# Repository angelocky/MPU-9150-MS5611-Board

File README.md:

MPU-9150-MS5611-Board
=====================
For the MPU-9150 and MS5611 Breakout Board. 

Arduino Library for the MPU-9150: [https://github.com/sparkfun/MPU-9150_Breakout/tree/master/firmware](https://github.com/sparkfun/MPU-9150_Breakout/tree/master/firmware)

Arduino Library for the MS5611 from Varesano.net: [http://www.varesano.net/files/FreeIMU-20121122_1126.zip](http://www.varesano.net/files/FreeIMU-20121122_1126.zip)

"MPU_9150_5611_example.ino" is an example sketch, to show functionality of the board. Individual example sketches can be found in their respective libraries.

Credit is due to the respective creators of the code.

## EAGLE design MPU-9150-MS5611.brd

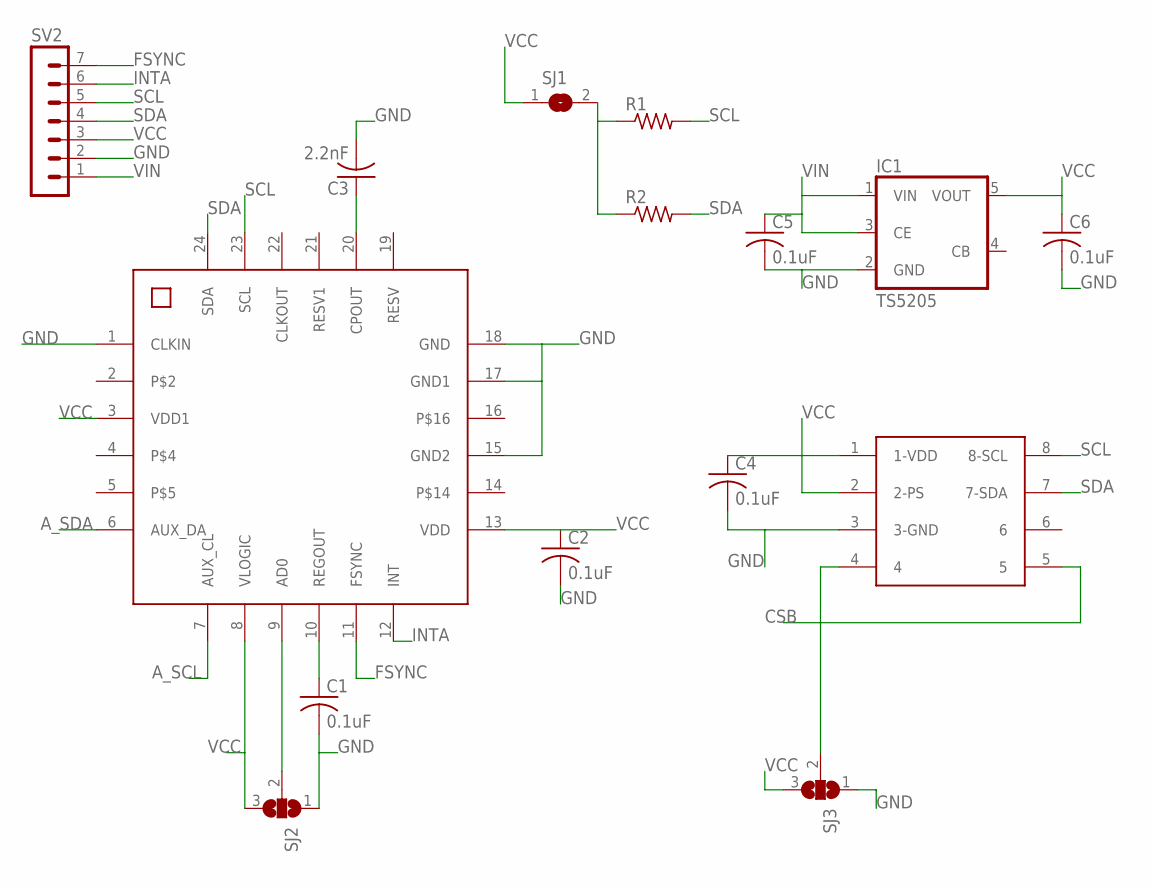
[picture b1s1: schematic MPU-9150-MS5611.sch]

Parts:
C1, C2, C4, C5, C6: 0.1uF; C0603
C3: 2.2nF; C0603
IC1: TS5205; SOT25
MPU-9150: MPU-9150MPU-9150; MPU-6050_QFN-24
MS5611: MS5611; MS5611-PACKAGE
R1, R2: R-US_R0603; R0603
SJ1: SJ
SJ2, SJ3: SJ2W; SJ_2
SV2: MA07-1

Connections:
9: MPU-9150.9 (AD0), SJ2.2
A_SCL: MPU-9150.7 (AUX_CL)
A_SDA: MPU-9150.6 (AUX_DA)
CSB: MS5611.4, MS5611.5, SJ3.2
FSYNC: MPU-9150.11 (FSYNC), SV2.7
GND: C1.2, C2.2, C3.2, C4.2, C5.2, C6.2, IC1.2 (GND), MPU-9150.1 (CLKIN), MPU-9150.15 (GND2), MPU-9150.17 (GND1), MPU-9150.18 (GND), MS5611.3 (3-GND), SJ2.1, SJ3.1, SV2.2
INTA: MPU-9150.12 (INT), SV2.6
unnamed: C1.1, MPU-9150.10 (REGOUT)
unnamed: C3.1, MPU-9150.20 (CPOUT)
PU: R1.1, R2.1, SJ1.2
SCL: MPU-9150.23 (SCL), MS5611.8 (8-SCL), R1.2, SV2.5
SDA: MPU-9150.24 (SDA), MS5611.7 (7-SDA), R2.2, SV2.4
VCC: C2.1, C4.1, C6.1, IC1.5 (VOUT), MPU-9150.3 (VDD1), MPU-9150.8 (VLOGIC), MPU-9150.13 (VDD), MS5611.1 (1-VDD), MS5611.2 (2-PS), SJ1.1, SJ2.3, SJ3.3, SV2.3
VIN: C5.1, IC1.1 (VIN), IC1.3 (CE), SV2.1

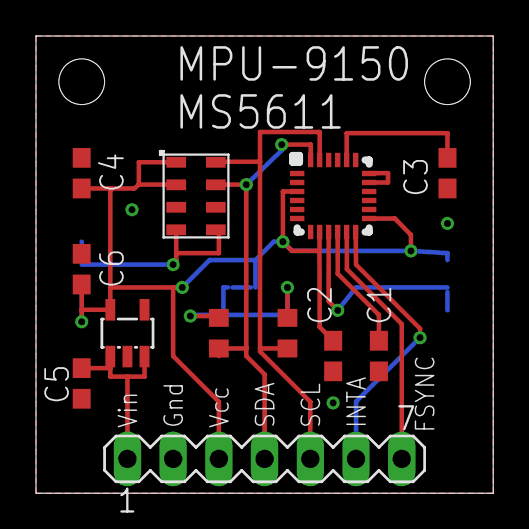
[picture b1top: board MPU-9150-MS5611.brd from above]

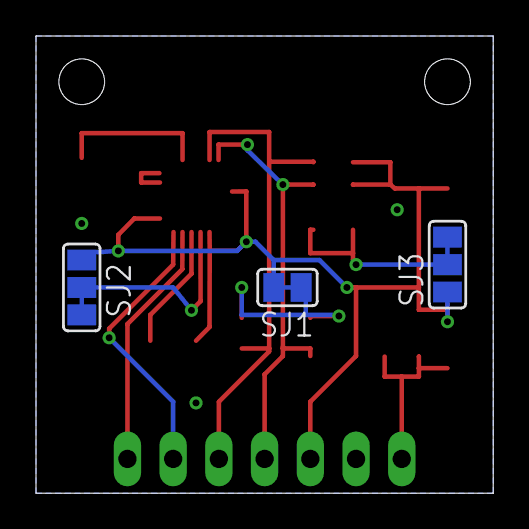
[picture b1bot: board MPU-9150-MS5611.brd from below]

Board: 2 copper layers, 25.4 x 25.4 mm, 15 parts (3 on the bottom side), 12 nets.
